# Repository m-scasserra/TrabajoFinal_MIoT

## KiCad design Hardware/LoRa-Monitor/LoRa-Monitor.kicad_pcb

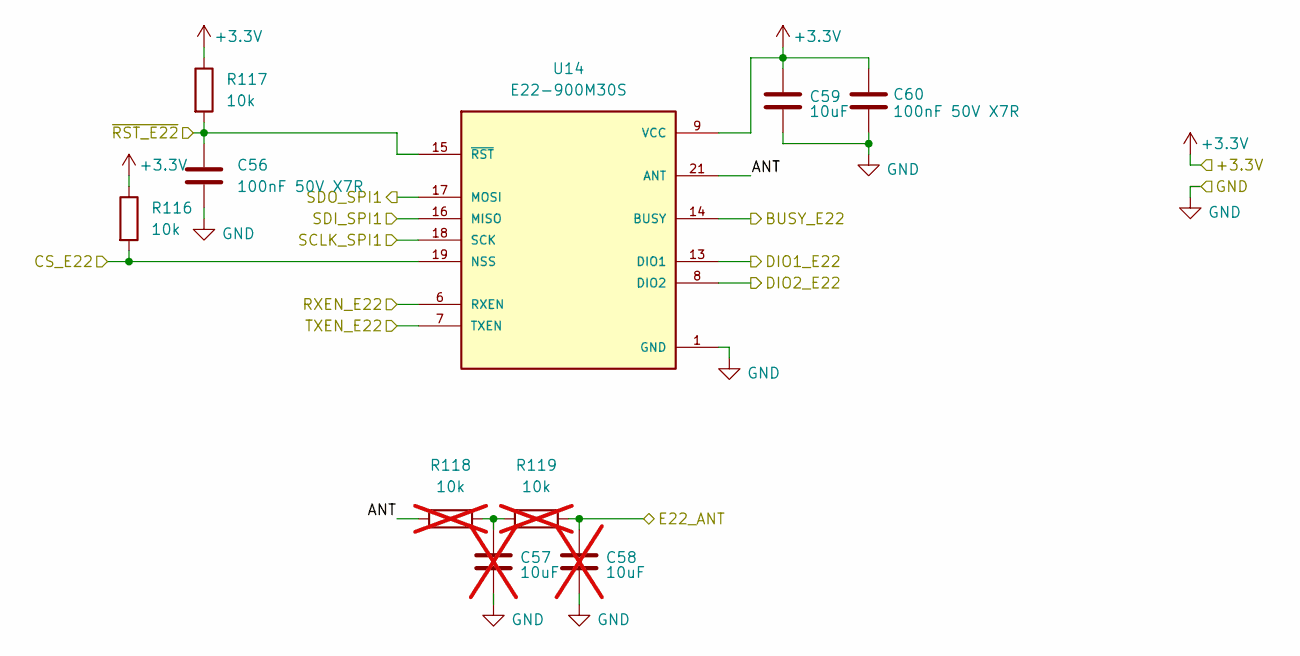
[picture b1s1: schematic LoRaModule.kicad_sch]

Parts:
C56, C60: 100nF 50V X7R; C_0805_2012Metric; LCSC Part # C49678
C57, C58: 10uF; C_0805_2012Metric; LCSC Part # C15850; not fitted
C59: 10uF; C_0805_2012Metric; LCSC Part # C15850
R116, R117: 10k; R_0805_2012Metric; LCSC Part # C17414
R118, R119: 10k; R_0805_2012Metric; LCSC Part # C17414; not fitted
U14: E22-900M30S; XCVR_E22-900M30S; LCSC Part # C411294

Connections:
+3.3V: C59.1, C60.1, R116.1, R117.1, U14.9 (VCC), U14.10 (VCC); also elsewhere on the board
/Connectors/E22_ANT: C58.1, R119.2; also elsewhere on the board
/LoRa Module/ANT: R118.1, U14.21 (ANT)
/LoRa Module/BUSY_E22: U14.14 (BUSY); also elsewhere on the board
/LoRa Module/CS_E22: R116.2, U14.19 (NSS); also elsewhere on the board
/LoRa Module/DIO1_E22: U14.13 (DIO1); also elsewhere on the board
/LoRa Module/DIO2_E22: U14.8 (DIO2); also elsewhere on the board
/LoRa Module/RXEN_E22: U14.6 (RXEN); also elsewhere on the board
/LoRa Module/TXEN_E22: U14.7 (TXEN); also elsewhere on the board
/LoRa Module/~RST_E22: C56.1, R117.2, U14.15 (~RST); also elsewhere on the board
/MCU/SCLK_SPI1: U14.18 (SCK); also elsewhere on the board
/MCU/SDI_SPI1: U14.16 (MISO); also elsewhere on the board
/MCU/SDO_SPI1: U14.17 (MOSI); also elsewhere on the board
GND: C56.2, C57.2, C58.2, C59.2, C60.2, U14.1 (GND), U14.2 (GND), U14.3 (GND), U14.4 (GND), U14.5 (GND), U14.11 (GND), U14.12 (GND), U14.20 (GND), U14.22 (GND); also elsewhere on the board
unnamed: C57.1, R118.2, R119.1

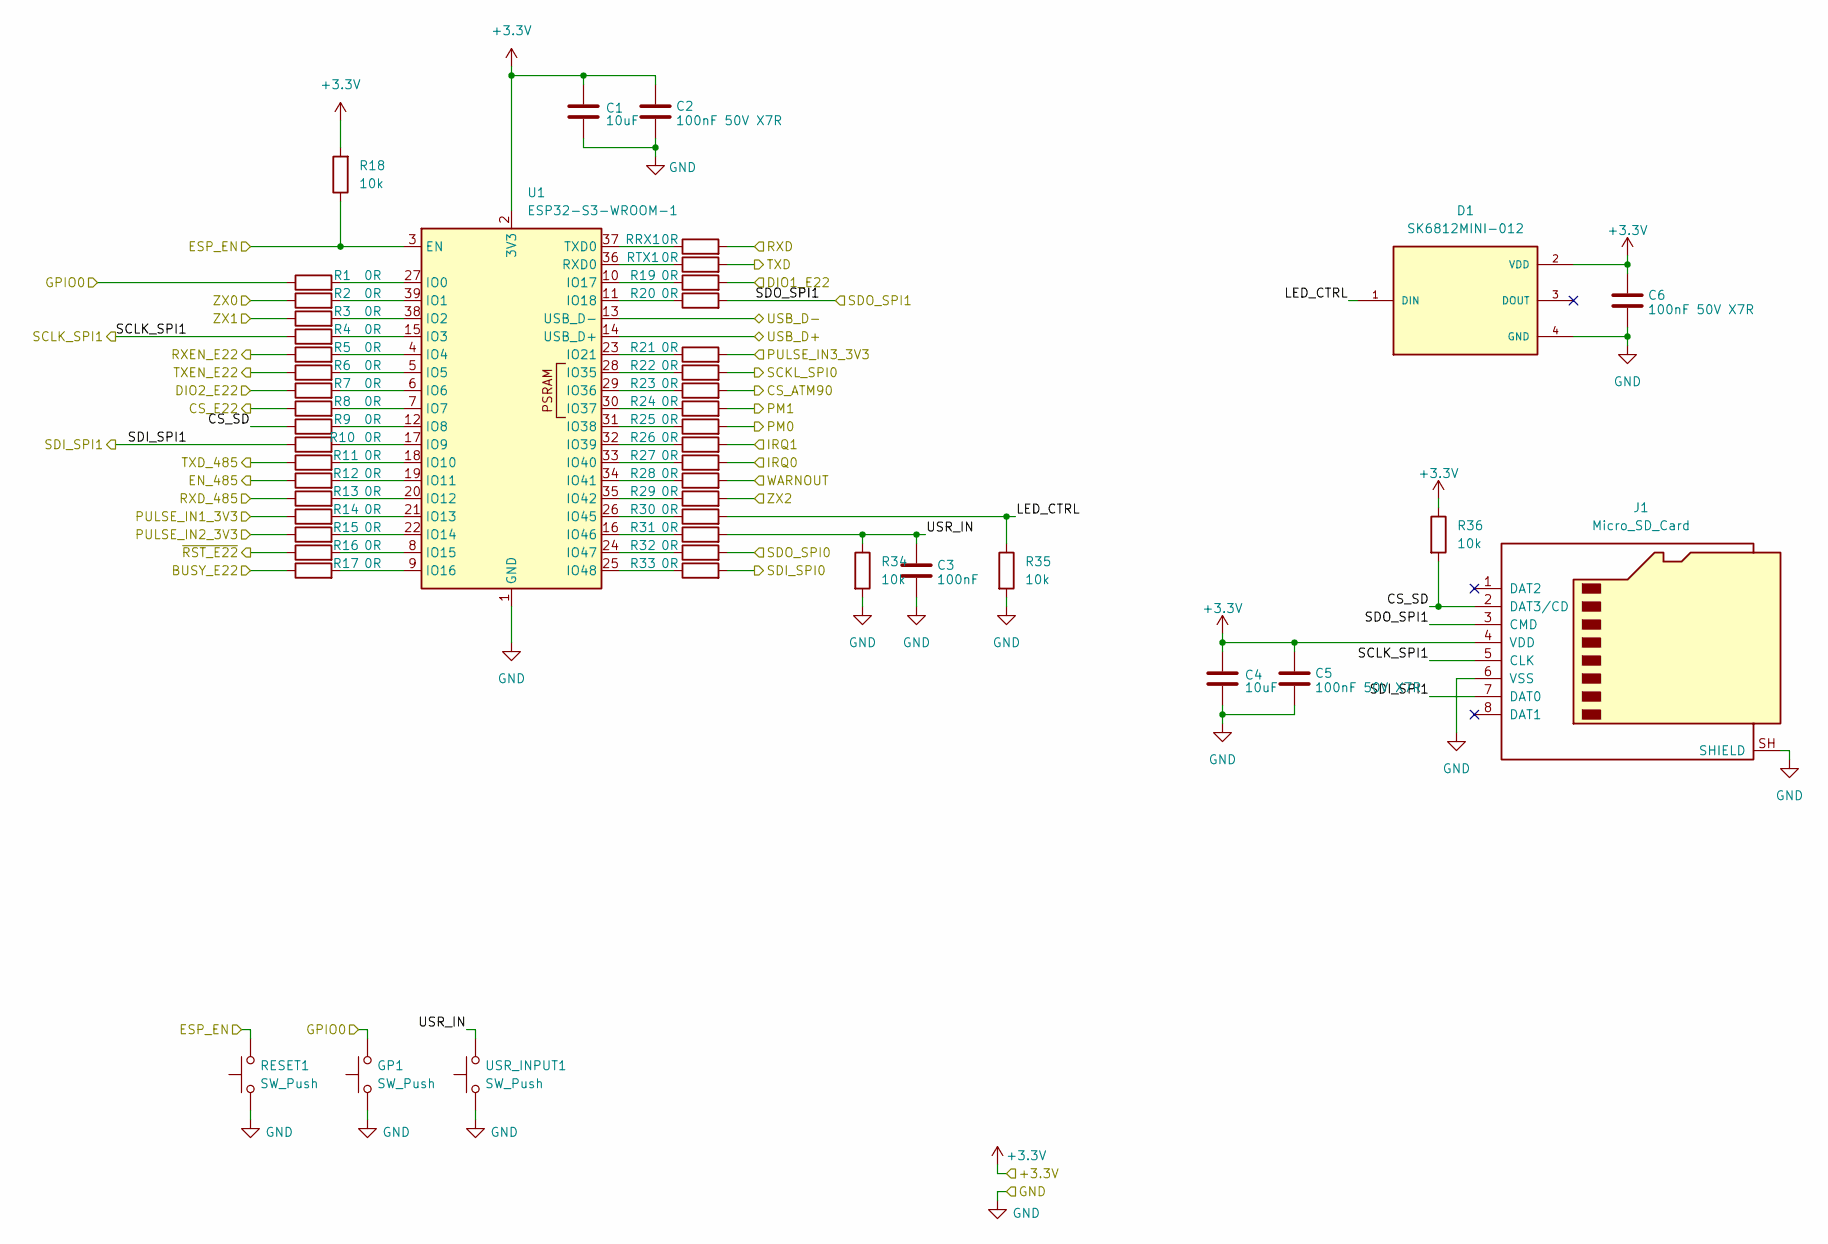
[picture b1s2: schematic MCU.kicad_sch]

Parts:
C1, C4: 10uF; C_0805_2012Metric; LCSC Part # C15850
C2, C5, C6: 100nF 50V X7R; C_0805_2012Metric; LCSC Part # C49678
C3: 100nF; C_0805_2012Metric; LCSC Part # C49678
D1: SK6812MINI-012; LED_SK6812MINI-012; LCSC Part # C2886570
GP1: SW_Push; SW_Push_1P1T_NO_CK_KMR2; LCSC Part # C72443
J1: Micro_SD_Card; microSD_HC_Molex_47219-2001; LCSC Part # C164170
R1, R2, R3, R4, R5, R6, R7, R8, R9, R10, R11, R12, R13, R14, R15, R16, R17, R19, R20, R21, R22, R23, R24, R25, R26, R27, R28, R29, R30, R31, R32, R33: 0R; R_0603_1608Metric; LCSC Part # C21189
R18, R34, R35, R36: 10k; R_0805_2012Metric; LCSC Part # C17414
RESET1: SW_Push; SW_Push_1P1T_NO_CK_KMR2; LCSC Part # C72443
RRX1: 0R; R_0603_1608Metric; LCSC Part # C21189
RTX1: 0R; R_0603_1608Metric; LCSC Part # C21189
U1: ESP32-S3-WROOM-1; LCSC Part # C2913205
USR_INPUT1: SW_Push; SW_Push_1P1T_NO_CK_KMR2; LCSC Part # C72443

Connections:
+3.3V: C1.1, C2.1, C4.1, C5.1, C6.1, D1.2 (VDD), J1.4 (VDD), R18.2, R36.1, U1.2 (3V3); also elsewhere on the board
/Connectors/ESP_EN: R18.1, RESET1.2, U1.3 (EN); also elsewhere on the board
/Connectors/GPIO0: GP1.2, R1.1; also elsewhere on the board
/Connectors/RXD: RRX1.2; also elsewhere on the board
/Connectors/TXD: RTX1.2; also elsewhere on the board
/Connectors/USB_D+: U1.14 (USB_D+); also elsewhere on the board
/Connectors/USB_D-: U1.13 (USB_D-); also elsewhere on the board
/Energy Meter Interface Module/EN_485: R12.1; also elsewhere on the board
/Energy Meter Interface Module/PULSE_IN1_3V3: R14.1; also elsewhere on the board
/Energy Meter Interface Module/PULSE_IN2_3V3: R15.1; also elsewhere on the board
/Energy Meter Interface Module/PULSE_IN3_3V3: R21.2; also elsewhere on the board
/Energy Meter Interface Module/RXD_485: R13.1; also elsewhere on the board
/Energy Meter Interface Module/TXD_485: R11.1; also elsewhere on the board
/Energy meter/CS_ATM90: R23.2; also elsewhere on the board
/Energy meter/IRQ0: R27.2; also elsewhere on the board
/Energy meter/IRQ1: R26.2; also elsewhere on the board
/Energy meter/PM0: R25.2; also elsewhere on the board
/Energy meter/PM1: R24.2; also elsewhere on the board
/Energy meter/SCKL_SPI0: R22.2; also elsewhere on the board
/Energy meter/SDI_SPI0: R33.2; also elsewhere on the board
/Energy meter/SDO_SPI0: R32.2; also elsewhere on the board
/Energy meter/WARNOUT: R28.2; also elsewhere on the board
/Energy meter/ZX0: R2.1; also elsewhere on the board
/Energy meter/ZX1: R3.1; also elsewhere on the board
/Energy meter/ZX2: R29.2; also elsewhere on the board
/LoRa Module/BUSY_E22: R17.1; also elsewhere on the board
/LoRa Module/CS_E22: R8.1; also elsewhere on the board
/LoRa Module/DIO1_E22: R19.2; also elsewhere on the board
/LoRa Module/DIO2_E22: R7.1; also elsewhere on the board
/LoRa Module/RXEN_E22: R5.1; also elsewhere on the board
/LoRa Module/TXEN_E22: R6.1; also elsewhere on the board
/LoRa Module/~RST_E22: R16.1; also elsewhere on the board
/MCU/CS_SD: J1.2 (DAT3/CD), R9.1, R36.2
/MCU/LED_CTRL: D1.1 (DIN), R30.2, R35.1
/MCU/SCLK_SPI1: J1.5 (CLK), R4.1; also elsewhere on the board
/MCU/SDI_SPI1: J1.7 (DAT0), R10.1; also elsewhere on the board
/MCU/SDO_SPI1: J1.3 (CMD), R20.2; also elsewhere on the board
/MCU/USR_IN: C3.1, R31.2, R34.1, USR_INPUT1.2
GND: C1.2, C2.2, C3.2, C4.2, C5.2, C6.2, D1.4 (GND), GP1.1, J1.6 (VSS), J1.SH (SHIELD), R34.2, R35.2, RESET1.1, U1.1 (GND), U1.40 (GND), U1.41 (GND), USR_INPUT1.1; also elsewhere on the board
unnamed: R1.2, U1.27 (IO0)
unnamed: R2.2, U1.39 (IO1)
unnamed: R3.2, U1.38 (IO2)
unnamed: R4.2, U1.15 (IO3)
unnamed: R5.2, U1.4 (IO4)
unnamed: R6.2, U1.5 (IO5)
unnamed: R7.2, U1.6 (IO6)
unnamed: R8.2, U1.7 (IO7)
unnamed: R9.2, U1.12 (IO8)
unnamed: R10.2, U1.17 (IO9)
unnamed: R11.2, U1.18 (IO10)
unnamed: R12.2, U1.19 (IO11)
unnamed: R13.2, U1.20 (IO12)
unnamed: R14.2, U1.21 (IO13)
unnamed: R15.2, U1.22 (IO14)
unnamed: R16.2, U1.8 (IO15)
unnamed: R17.2, U1.9 (IO16)
unnamed: R19.1, U1.10 (IO17)
unnamed: R20.1, U1.11 (IO18)
unnamed: R21.1, U1.23 (IO21)
unnamed: R22.1, U1.28 (IO35)
unnamed: R23.1, U1.29 (IO36)
unnamed: R24.1, U1.30 (IO37)
unnamed: R25.1, U1.31 (IO38)
unnamed: R26.1, U1.32 (IO39)
unnamed: R27.1, U1.33 (IO40)
unnamed: R28.1, U1.34 (IO41)
unnamed: R29.1, U1.35 (IO42)
unnamed: R30.1, U1.26 (IO45)
unnamed: R31.1, U1.16 (IO46)
unnamed: R32.1, U1.24 (IO47)
unnamed: R33.1, U1.25 (IO48)
unnamed: RTX1.1, U1.36 (RXD0)
unnamed: RRX1.1, U1.37 (TXD0)

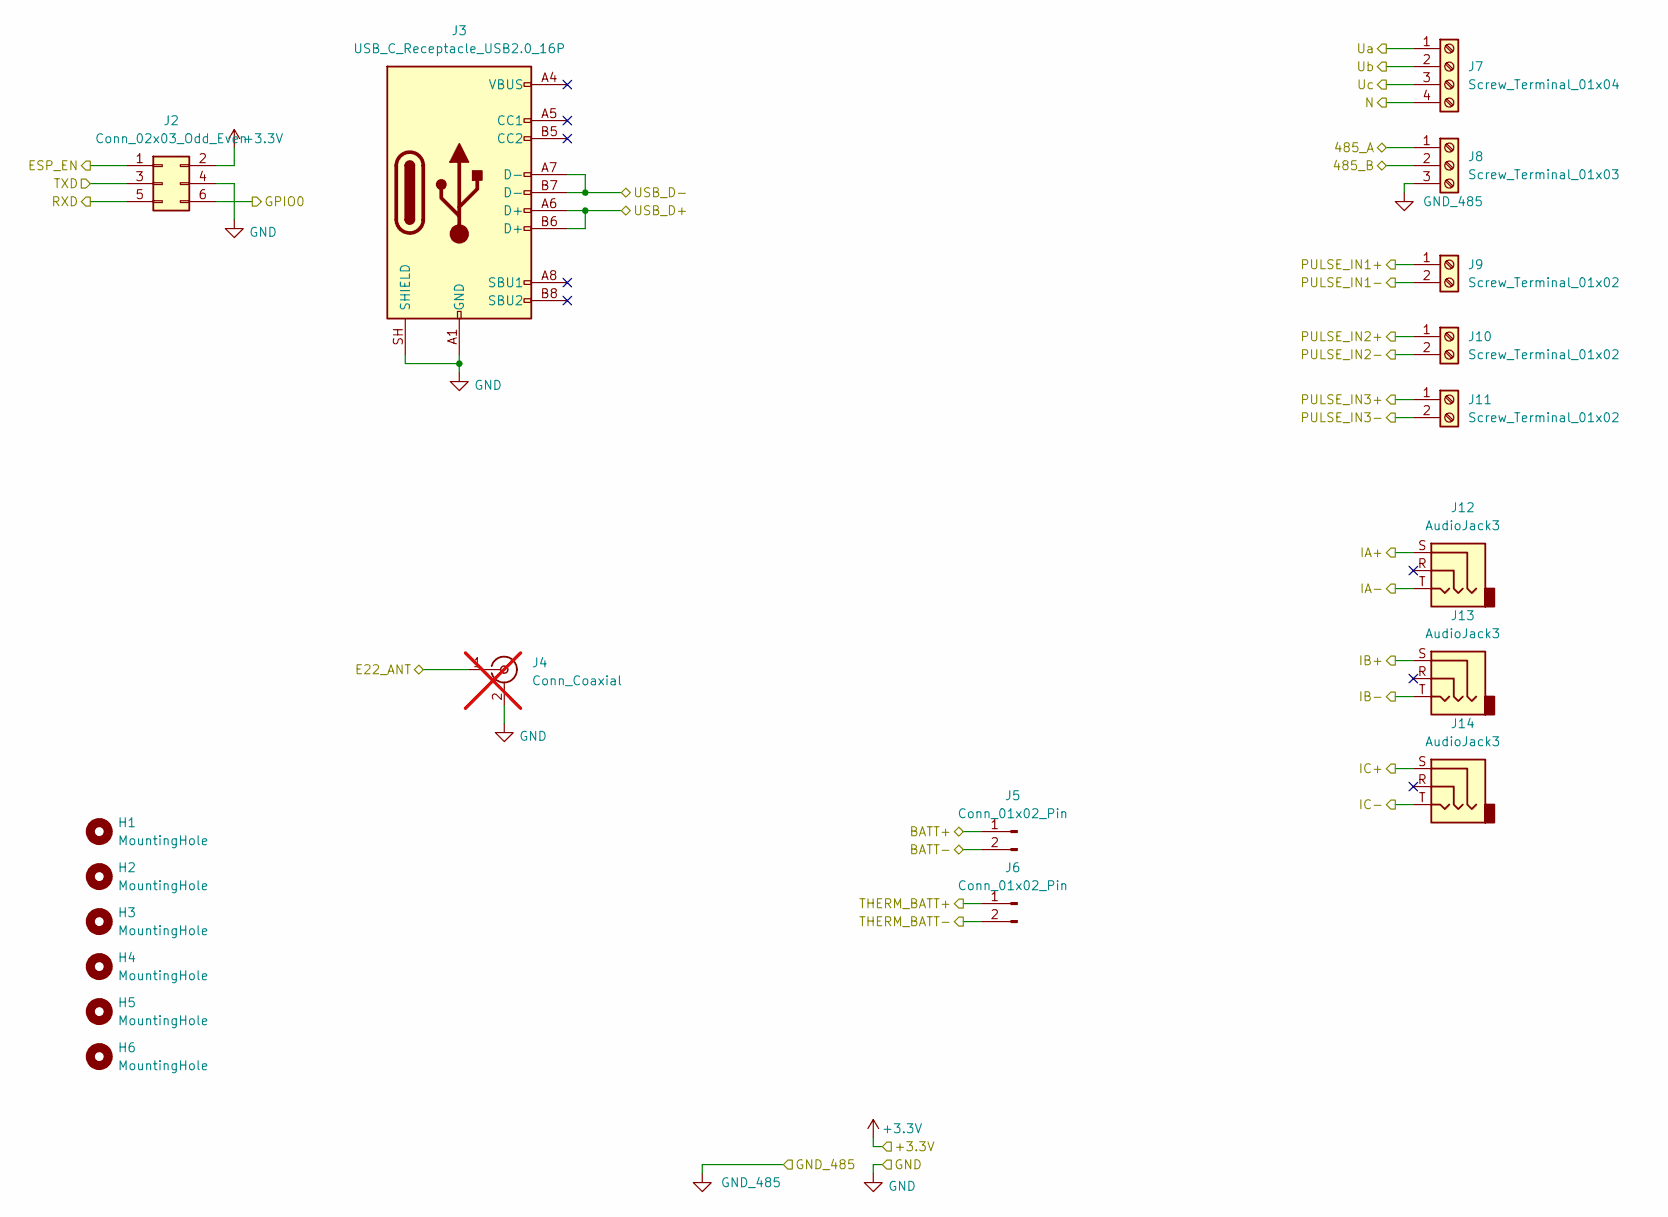
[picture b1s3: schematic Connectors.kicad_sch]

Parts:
H1, H2, H3, H4, H5, H6: MountingHole; MountingHole_3.2mm_M3_DIN965
J2: Conn_02x03_Odd_Even; PinHeader_2x03_P2.54mm_Vertical
J3: USB_C_Receptacle_USB2.0_16P; USB_C_Receptacle_HRO_TYPE-C-31-M-12; LCSC Part # C165948
J4: Conn_Coaxial; U.FL_Molex_MCRF_73412-0110_Vertical; LCSC Part # C434806; not fitted
J5, J6: Conn_01x02_Pin; JST_PH_B2B-PH-K_1x02_P2.00mm_Vertical; LCSC Part # C131337
J7: Screw_Terminal_01x04; TerminalBlock_Phoenix_PT-1,5-4-5.0-H_1x04_P5.00mm_Horizontal; LCSC Part # C3817931
J8: Screw_Terminal_01x03; TerminalBlock_Phoenix_PT-1,5-3-5.0-H_1x03_P5.00mm_Horizontal; LCSC Part # C3816891
J9, J10, J11: Screw_Terminal_01x02; TerminalBlock_Phoenix_PT-1,5-2-5.0-H_1x02_P5.00mm_Horizontal; LCSC Part # C3819953
J12, J13, J14: AudioJack3; Jack_3.5mm_CUI_SJ1-3523N_Horizontal; LCSC Part # C20182914

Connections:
+3.3V: J2.2; also elsewhere on the board
/Connectors/485_A: J8.1; also elsewhere on the board
/Connectors/485_B: J8.2; also elsewhere on the board
/Connectors/BATT+: J5.1; also elsewhere on the board
/Connectors/E22_ANT: J4.1 (In); also elsewhere on the board
/Connectors/ESP_EN: J2.1; also elsewhere on the board
/Connectors/GPIO0: J2.6; also elsewhere on the board
/Connectors/IA+: J12.S; also elsewhere on the board
/Connectors/IA-: J12.T; also elsewhere on the board
/Connectors/IB+: J13.S; also elsewhere on the board
/Connectors/IB-: J13.T; also elsewhere on the board
/Connectors/IC+: J14.S; also elsewhere on the board
/Connectors/IC-: J14.T; also elsewhere on the board
/Connectors/PULSE_IN1+: J9.1; also elsewhere on the board
/Connectors/PULSE_IN1-: J9.2; also elsewhere on the board
/Connectors/PULSE_IN2+: J10.1; also elsewhere on the board
/Connectors/PULSE_IN2-: J10.2; also elsewhere on the board
/Connectors/PULSE_IN3+: J11.1; also elsewhere on the board
/Connectors/PULSE_IN3-: J11.2; also elsewhere on the board
/Connectors/RXD: J2.5; also elsewhere on the board
/Connectors/THERM_BATT+: J6.1; also elsewhere on the board
/Connectors/TXD: J2.3; also elsewhere on the board
/Connectors/USB_D+: J3.A6 (D+), J3.B6 (D+); also elsewhere on the board
/Connectors/USB_D-: J3.A7 (D-), J3.B7 (D-); also elsewhere on the board
/Connectors/Ua: J7.1; also elsewhere on the board
/Connectors/Ub: J7.2; also elsewhere on the board
/Connectors/Uc: J7.3; also elsewhere on the board
GND: J2.4, J3.A1 (GND), J3.A12 (GND), J3.B1 (GND), J3.B12 (GND), J3.SH (SHIELD), J4.2 (Ext), J5.2, J6.2; also elsewhere on the board
GND_485: J8.3; also elsewhere on the board
GND_M90: J7.4; also elsewhere on the board

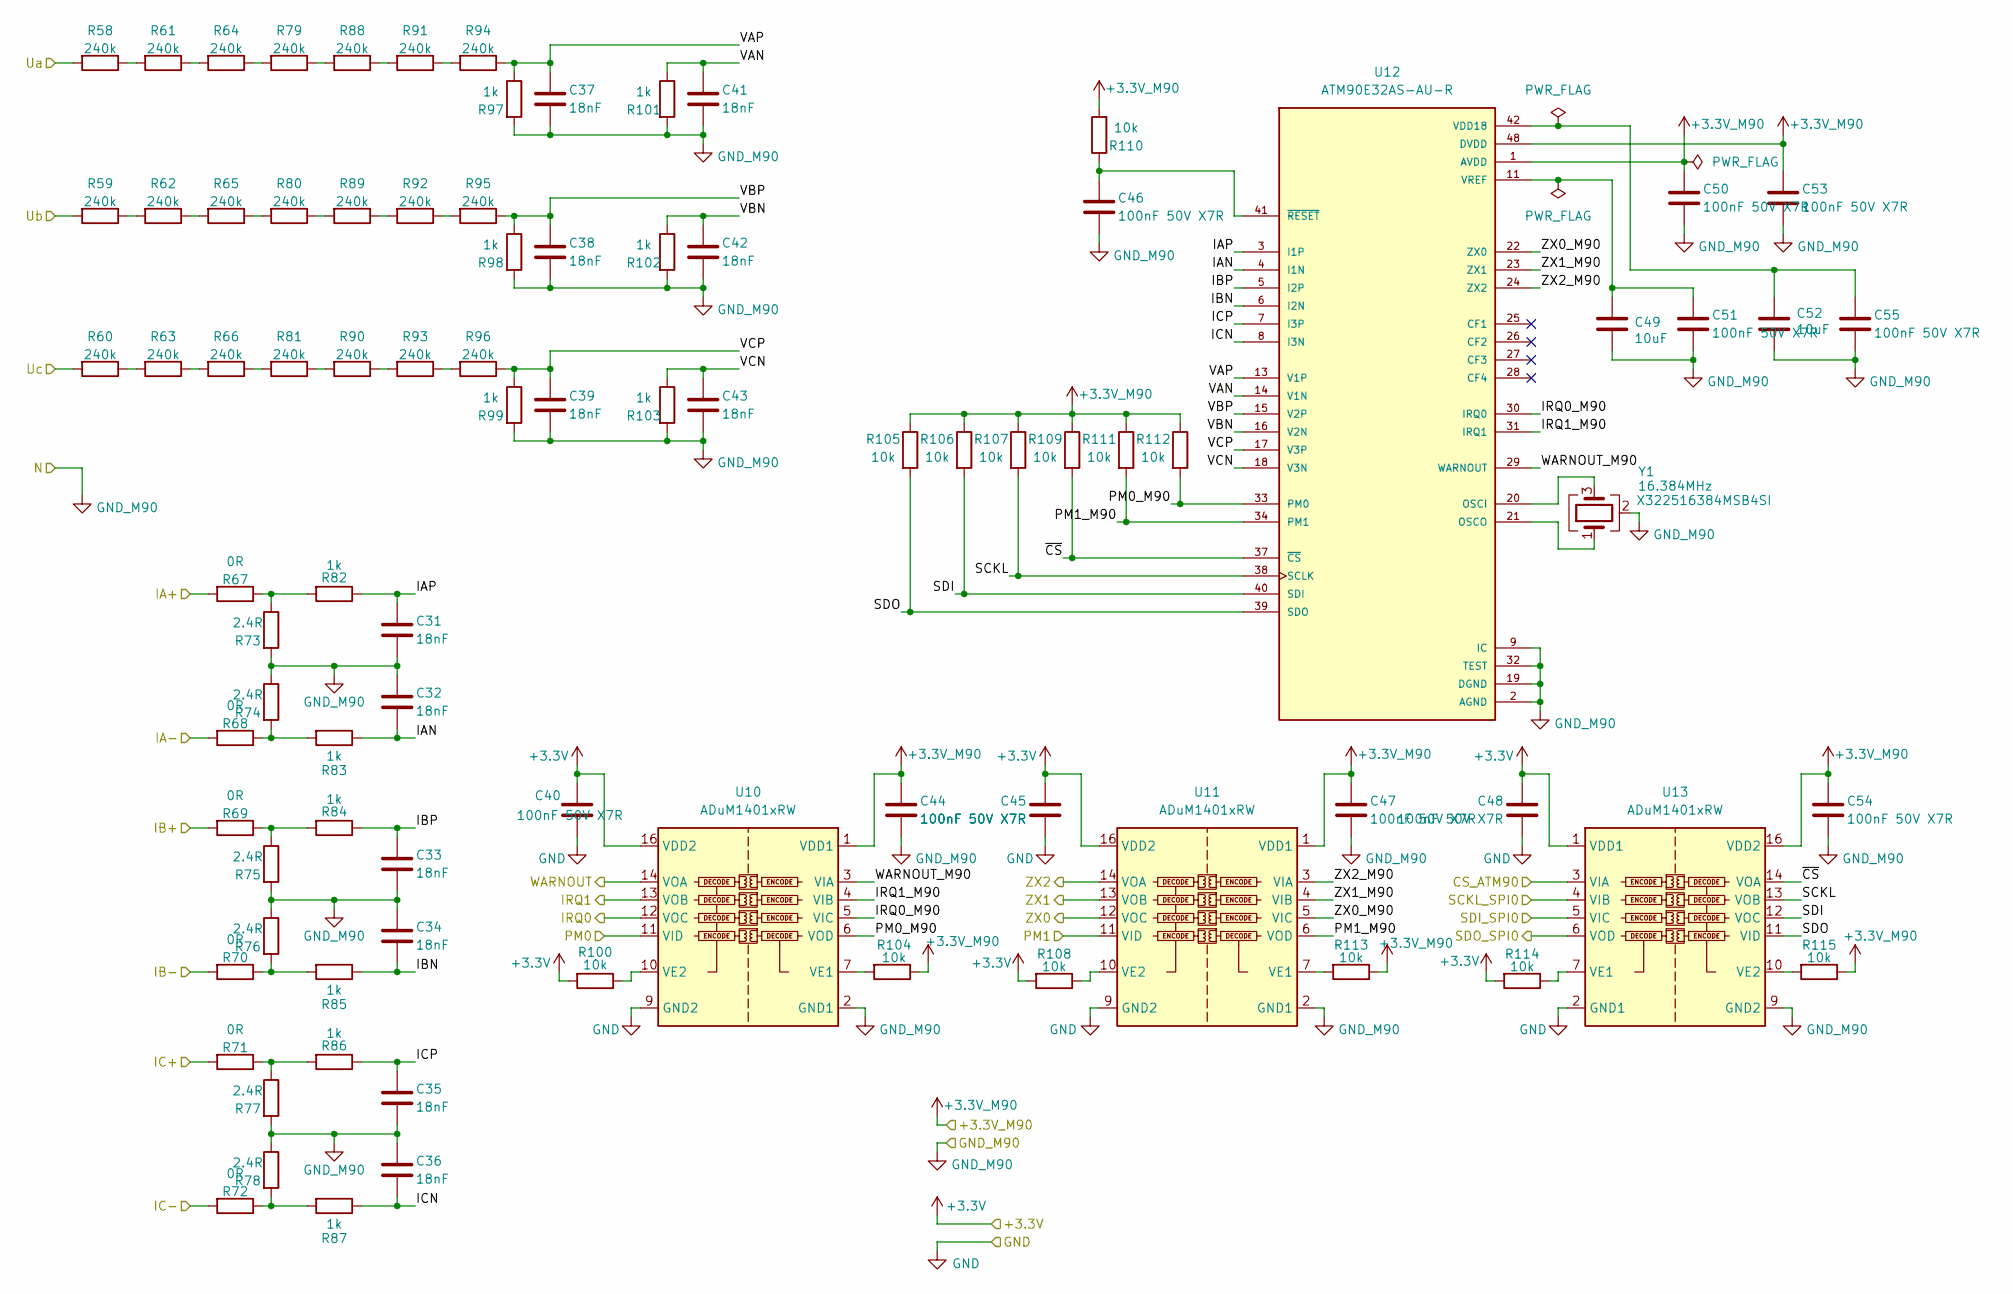
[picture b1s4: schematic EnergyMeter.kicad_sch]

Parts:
C31, C32, C33, C34, C35, C36, C37, C38, C39, C41, C42, C43: 18nF; C_0805_2012Metric; LCSC Part # C1723
C40, C44, C45, C46, C47, C48, C50, C51, C53, C54, C55: 100nF 50V X7R; C_0805_2012Metric; LCSC Part # C49678
C49, C52: 10uF; C_0805_2012Metric; LCSC Part # C15850
R58, R59, R60, R61, R62, R63, R64, R65, R66, R79, R80, R81, R88, R89, R90, R91, R92, R93, R94, R95, R96: 240k; R_1206_3216Metric; LCSC Part # C18001
R67, R68, R69, R70, R71, R72: 0R; R_0805_2012Metric; LCSC Part # C17477
R73, R74, R75, R76, R77, R78: 2.4R; R_0805_2012Metric; LCSC Part # C17528
R82, R83, R84, R85, R86, R87, R97, R98, R99, R101, R102, R103: 1k; R_0805_2012Metric; LCSC Part # C17513
R100, R104, R105, R106, R107, R108, R109, R110, R111, R112, R113, R114, R115: 10k; R_0805_2012Metric; LCSC Part # C17414
U10, U11, U13: ADuM1401xRW; SOIC-16W_7.5x10.3mm_P1.27mm; LCSC Part # C91762
U12: ATM90E32AS-AU-R; QFP50P900X900X120-48N; LCSC Part # C177153
Y1: 16.384MHz; Crystal_SMD_3225-4Pin_3.2x2.5mm; Part # X322516384MSB4SI; LCSC Part # C13739

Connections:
+3.3V: C40.1, C45.1, C48.1, R100.2, R108.2, R114.2, U10.16 (VDD2), U11.16 (VDD2), U13.1 (VDD1); also elsewhere on the board
+3.3V_M90: C44.1, C47.1, C50.1, C53.1, C54.1, R104.1, R105.1, R106.1, R107.1, R109.1, R110.2, R111.1, R112.1, R113.1, R115.1, U10.1 (VDD1), U11.1 (VDD1), U12.1 (AVDD), U12.48 (DVDD), U13.16 (VDD2); also elsewhere on the board
/Connectors/IA+: R67.2; also elsewhere on the board
/Connectors/IA-: R68.2; also elsewhere on the board
/Connectors/IB+: R69.2; also elsewhere on the board
/Connectors/IB-: R70.2; also elsewhere on the board
/Connectors/IC+: R71.2; also elsewhere on the board
/Connectors/IC-: R72.2; also elsewhere on the board
/Connectors/Ua: R58.2; also elsewhere on the board
/Connectors/Ub: R59.2; also elsewhere on the board
/Connectors/Uc: R60.2; also elsewhere on the board
/Energy meter/CS_ATM90: U13.3 (VIA); also elsewhere on the board
/Energy meter/IAN: C32.2, R83.1, U12.4 (I1N)
/Energy meter/IAP: C31.1, R82.1, U12.3 (I1P)
/Energy meter/IBN: C34.2, R85.1, U12.6 (I2N)
/Energy meter/IBP: C33.1, R84.1, U12.5 (I2P)
/Energy meter/ICN: C36.2, R87.1, U12.8 (I3N)
/Energy meter/ICP: C35.1, R86.1, U12.7 (I3P)
/Energy meter/IRQ0: U10.12 (VOC); also elsewhere on the board
/Energy meter/IRQ0_M90: U10.5 (VIC), U12.30 (IRQ0)
/Energy meter/IRQ1: U10.13 (VOB); also elsewhere on the board
/Energy meter/IRQ1_M90: U10.4 (VIB), U12.31 (IRQ1)
/Energy meter/PM0: U10.11 (VID); also elsewhere on the board
/Energy meter/PM0_M90: R112.2, U10.6 (VOD), U12.33 (PM0)
/Energy meter/PM1: U11.11 (VID); also elsewhere on the board
/Energy meter/PM1_M90: R111.2, U11.6 (VOD), U12.34 (PM1)
/Energy meter/SCKL: R107.2, U12.38 (SCLK), U13.13 (VOB)
/Energy meter/SCKL_SPI0: U13.4 (VIB); also elsewhere on the board
/Energy meter/SDI: R106.2, U12.40 (SDI), U13.12 (VOC)
/Energy meter/SDI_SPI0: U13.5 (VIC); also elsewhere on the board
/Energy meter/SDO: R105.2, U12.39 (SDO), U13.11 (VID)
/Energy meter/SDO_SPI0: U13.6 (VOD); also elsewhere on the board
/Energy meter/VAN: C41.1, R101.1, U12.14 (V1N)
/Energy meter/VAP: C37.1, R94.1, R97.1, U12.13 (V1P)
/Energy meter/VBN: C42.1, R102.1, U12.16 (V2N)
/Energy meter/VBP: C38.1, R95.1, R98.1, U12.15 (V2P)
/Energy meter/VCN: C43.1, R103.1, U12.18 (V3N)
/Energy meter/VCP: C39.1, R96.1, R99.1, U12.17 (V3P)
/Energy meter/WARNOUT: U10.14 (VOA); also elsewhere on the board
/Energy meter/WARNOUT_M90: U10.3 (VIA), U12.29 (WARNOUT)
/Energy meter/ZX0: U11.12 (VOC); also elsewhere on the board
/Energy meter/ZX0_M90: U11.5 (VIC), U12.22 (ZX0)
/Energy meter/ZX1: U11.13 (VOB); also elsewhere on the board
/Energy meter/ZX1_M90: U11.4 (VIB), U12.23 (ZX1)
/Energy meter/ZX2: U11.14 (VOA); also elsewhere on the board
/Energy meter/ZX2_M90: U11.3 (VIA), U12.24 (ZX2)
/Energy meter/~CS: R109.2, U12.37 (~CS), U13.14 (VOA)
GND: C40.2, C45.2, C48.2, U10.9 (GND2), U10.15 (GND2), U11.9 (GND2), U11.15 (GND2), U13.2 (GND1), U13.8 (GND1); also elsewhere on the board
GND_M90: C31.2, C32.1, C33.2, C34.1, C35.2, C36.1, C37.2, C38.2, C39.2, C41.2, C42.2, C43.2, C44.2, C46.2, C47.2, C49.2, C50.2, C51.2, C52.2, C53.2, C54.2, C55.2, R73.2, R74.1, R75.2, R76.1, R77.2, R78.1, R97.2, R98.2, R99.2, R101.2, R102.2, R103.2, U10.2 (GND1), U10.8 (GND1), U11.2 (GND1), U11.8 (GND1), U12.2 (AGND), U12.9 (IC), U12.10 (IC), U12.12 (AGND), U12.19 (DGND), U12.32 (TEST), U12.36 (IC), U12.44 (DGND), U12.47 (DGND), U13.9 (GND2), U13.15 (GND2), Y1.2 (G), Y1.4 (G); also elsewhere on the board
unnamed: R58.1, R61.2
unnamed: R59.1, R62.2
unnamed: R60.1, R63.2
unnamed: R61.1, R64.2
unnamed: R62.1, R65.2
unnamed: R63.1, R66.2
unnamed: R64.1, R79.2
unnamed: R65.1, R80.2
unnamed: R66.1, R81.2
unnamed: R67.1, R73.1, R82.2
unnamed: R68.1, R74.2, R83.2
unnamed: R69.1, R75.1, R84.2
unnamed: R70.1, R76.2, R85.2
unnamed: R71.1, R77.1, R86.2
unnamed: R72.1, R78.2, R87.2
unnamed: R79.1, R88.2
unnamed: R80.1, R89.2
unnamed: R81.1, R90.2
unnamed: R88.1, R91.2
unnamed: R89.1, R92.2
unnamed: R90.1, R93.2
unnamed: R91.1, R94.2
unnamed: R92.1, R95.2
unnamed: R93.1, R96.2
unnamed: R104.2, U10.7 (VE1)
unnamed: R100.1, U10.10 (VE2)
unnamed: R113.2, U11.7 (VE1)
unnamed: R108.1, U11.10 (VE2)
unnamed: U12.20 (OSCI), Y1.3
unnamed: U12.21 (OSCO), Y1.1
unnamed: C49.1, C51.1, U12.11 (VREF)
unnamed: C46.1, R110.1, U12.41 (~RESET)
unnamed: R114.1, U13.7 (VE1)
unnamed: R115.2, U13.10 (VE2)
VDD18: C52.1, C55.1, U12.42 (VDD18), U12.43 (VDD18)

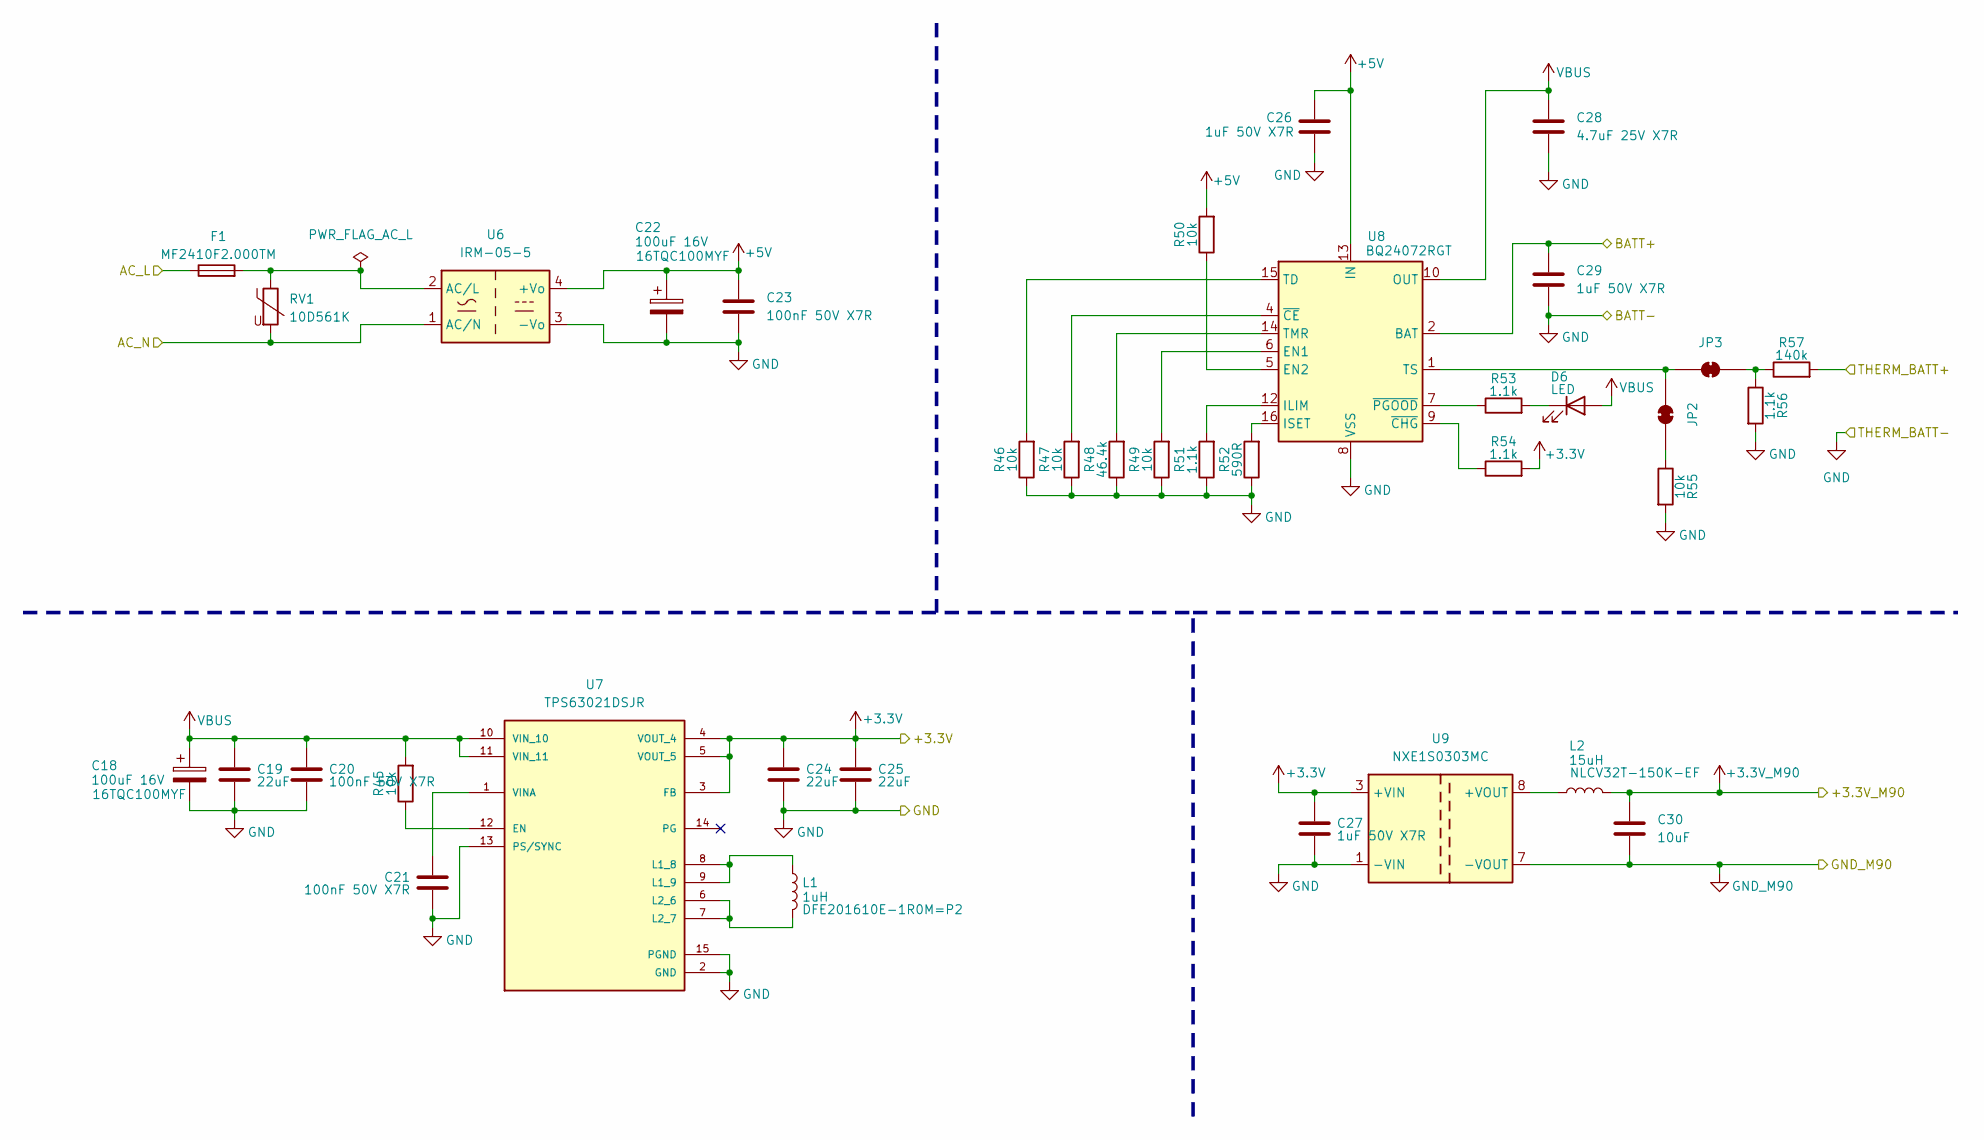
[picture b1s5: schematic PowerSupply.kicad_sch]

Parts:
C18, C22: 100uF 16V; CP_EIA-7343-31_Kemet-D; Part # 16TQC100MYF; LCSC Part # C7223
C19, C24, C25: 22uF; C_0805_2012Metric; LCSC Part # C45783
C20, C21, C23: 100nF 50V X7R; C_0805_2012Metric; LCSC Part # C49678
C26, C27, C29: 1uF 50V X7R; C_0805_2012Metric; LCSC Part # C28323
C28: 4.7uF 25V X7R; C_0805_2012Metric; LCSC Part # C1779
C30: 10uF; C_0805_2012Metric; LCSC Part # C15850
D6: LED; LED_0805_2012Metric; LCSC Part # C84256
F1: MF2410F2.000TM; Fuse_2410_6125Metric; LCSC Part # C83797
JP2, JP3: SolderJumper_2_Bridged; SolderJumper-2_P1.3mm_Bridged_RoundedPad1.0x1.5mm
L1: 1uH; L_0806_2016Metric; Part # DFE201610E-1R0M=P2; LCSC Part # C161082
L2: 15uH; L_1210_3225Metric_Pad1.42x2.65mm_HandSolder; Part # NLCV32T-150K-EF; LCSC Part # C250232
R45, R46, R47, R49, R50, R55: 10k; R_0805_2012Metric; LCSC Part # C17414
R48: 46.4k; R_0805_2012Metric; LCSC Part # C483162
R51, R53, R54, R56: 1.1k; R_0805_2012Metric; LCSC Part # C185294
R52: 590R; R_0805_2012Metric; LCSC Part # C55566
R57: 140k; R_0805_2012Metric; LCSC Part # C17460
RV1: 10D561K; RV_Disc_D12mm_W6.1mm_P7.5mm; LCSC Part # C2656193
U6: IRM-05-5; Converter_ACDC_MeanWell_IRM-05-xx_THT; LCSC Part # C48603696
U7: TPS63021DSJR; IC_TPS63021DSJR; LCSC Part # C202140
U8: BQ24072RGT; VQFN-16-1EP_3x3mm_P0.5mm_EP1.6x1.6mm; LCSC Part # C140288
U9: NXE1S0303MC; Converter_DCDC_Murata_NXExSxxxxMC_SMD; LCSC Part # C20606969

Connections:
+3.3V: C24.1, C25.1, C27.1, R54.2, U7.3 (FB), U7.4 (VOUT_4), U7.5 (VOUT_5), U9.3 (+VIN); also elsewhere on the board
+3.3V_M90: C30.1, L2.2; also elsewhere on the board
+5V: C22.1, C23.1, C26.1, R50.2, U6.4 (+Vo), U8.13 (IN)
/Connectors/BATT+: C29.1, U8.2 (BAT), U8.3 (BAT); also elsewhere on the board
/Connectors/THERM_BATT+: R57.2; also elsewhere on the board
/Connectors/Ua: F1.1; also elsewhere on the board
GND: C18.2, C19.2, C20.2, C21.2, C22.2, C23.2, C24.2, C25.2, C26.2, C27.2, C28.2, C29.2, R46.1, R47.1, R48.1, R49.1, R51.1, R52.1, R55.2, R56.2, U6.3 (-Vo), U7.2 (GND), U7.13 (PS/SYNC), U7.15 (PGND), U7.16 (GND), U7.17 (GND), U7.18 (GND), U7.19 (GND), U7.20 (GND), U7.21 (GND), U7.22 (GND), U7.23 (GND), U7.24 (GND), U7.25 (GND), U7.26 (GND), U7.27 (GND), U7.28 (GND), U7.29 (GND), U7.30 (GND), U8.8 (VSS), U8.17 (VSS), U9.1 (-VIN); also elsewhere on the board
GND_M90: C30.2, RV1.2, U6.1 (AC/N), U9.7 (-VOUT); also elsewhere on the board
unnamed: D6.1 (K), R53.2
unnamed: JP2.1 (A), R55.1
unnamed: JP2.2 (B), JP3.2 (B), U8.1 (TS)
unnamed: JP3.1 (A), R56.1, R57.1
unnamed: F1.2, RV1.1, U6.2 (AC/L)
unnamed: R45.1, U7.12 (EN)
unnamed: L1.1, U7.8 (L1_8), U7.9 (L1_9)
unnamed: L1.2, U7.6 (L2_6), U7.7 (L2_7)
unnamed: C21.1, U7.1 (VINA)
unnamed: R49.2, U8.6 (EN1)
unnamed: R50.1, U8.5 (EN2)
unnamed: R51.2, U8.12 (ILIM)
unnamed: R52.2, U8.16 (ISET)
unnamed: R46.2, U8.15 (TD)
unnamed: R48.2, U8.14 (TMR)
unnamed: R47.2, U8.4 (~CE)
unnamed: R54.1, U8.9 (~CHG)
unnamed: R53.1, U8.7 (~PGOOD)
unnamed: L2.1, U9.8 (+VOUT)
VBUS: C18.1, C19.1, C20.1, C28.1, D6.2 (A), R45.2, U7.10 (VIN_10), U7.11 (VIN_11), U8.10 (OUT), U8.11 (OUT)
